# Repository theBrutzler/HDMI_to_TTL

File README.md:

# HDMI_to_TTL

HDMI-Ausgang für das R1gol DS1054Z: Das parallele 24-Bit-RGB-Signal (800 × 480), das vom Mainboard zum internen Display geht, wird abgegriffen und von einem **Tang Nano 9K** (Gowin GW1NR-9C) in ein HDMI-Signal umgewandelt.

*HDMI output for the R1gol DS1054Z: the parallel 24-bit RGB signal (800 × 480) running from the mainboard to the internal display is tapped and converted into an HDMI signal by a **Tang Nano 9K** (Gowin GW1NR-9C).*

Diese Anleitung beschreibt, wie die Platine bestückt und der FPGA programmiert wird.

*This guide describes how to assemble the board and program the FPGA.*

> ⚠️ **Haftungsausschluss:** Nachbau, Programmierung und Einbau erfolgen **auf eigene Gefahr**. Für das Öffnen des Oszilloskops wird ein Eingriff in das Gerät nötig, der zum Verlust der Garantie führen kann. Für Schäden am Oszilloskop, am Tang Nano 9K, an angeschlossenen Geräten oder sonstige Folgeschäden wird **keine Haftung übernommen**.
>
> *⚠️ **Disclaimer:** Building, programming and installing this modification is done **at your own risk**. Opening the oscilloscope requires modifying the device, which may void its warranty. **No liability is accepted** for damage to the oscilloscope, the Tang Nano 9K, connected devices or any other consequential damage.*

---

## Inhalt / *Contents*

1. [Benötigte Teile / *Required parts*](#1-benötigte-teile--required-parts)
2. [Die Platine / *The PCB*](#2-die-platine--the-pcb)
3. [Platine trennen / *Breaking the PCB apart*](#3-platine-trennen--breaking-the-pcb-apart)
4. [Tang Nano 9K bestücken / *Mounting the Tang Nano 9K*](#4-tang-nano-9k-bestücken--mounting-the-tang-nano-9k)
5. [FPGA programmieren / *Programming the FPGA*](#5-fpga-programmieren--programming-the-fpga)
6. [Einbau ins Oszilloskop / *Installation in the oscilloscope*](#6-einbau-ins-oszilloskop--installation-in-the-oscilloscope)
7. [Fehlersuche (LEDs und UART) / *Troubleshooting (LEDs and UART)*](#7-fehlersuche-leds-und-uart--troubleshooting-leds-and-uart)

---

## 1. Benötigte Teile / *Required parts*

| Teil / *Part* | Bemerkung / *Notes* |
|---|---|
| Platine `TTL_to_HDMI`<br>*PCB `TTL_to_HDMI`* | Display-Teil und FPGA-Teil hängen als ein Nutzen zusammen<br>*Display part and FPGA part come as one panel* |
| Tang Nano 9K | Sipeed, FPGA GW1NR-LV9QN88PC6/I5 |
| 2 × Stiftleiste 1 × 24, Raster 2,54 mm<br>*2 × pin header 1 × 24, 2.54 mm pitch* | für den Tang Nano 9K (liegen dem Board meist bei)<br>*for the Tang Nano 9K (usually included with the board)* |
| Buchsenleiste 1 × 2, Raster 2,54 mm<br>*Female header 1 × 2, 2.54 mm pitch* | J1, holt die 5 V von der Stiftleiste des Mainboards<br>*J1, picks up 5 V from the mainboard pin header* |
| FFC-Kabel 50-polig, Raster 0,5 mm<br>*FFC cable 50-pin, 0.5 mm pitch* | verbindet Mainboard und Display-Teil („To Mainboard“)<br>*connects mainboard and display part ("To Mainboard")* |
| FFC-Kabel 35-polig, Raster 0,5 mm<br>*FFC cable 35-pin, 0.5 mm pitch* | verbindet Display-Teil (J5) und FPGA-Teil (J3)<br>*connects display part (J5) and FPGA part (J3)* |
| HDMI-Einbau-Verlängerung mit 90°-Winkelstecker<br>*Panel-mount HDMI extension with 90° angled plug* | Buchse zum Festschrauben im Gehäuse, Stecker in den Tang Nano 9K (siehe [Abschnitt 6.3](#63-hdmi-buchse-im-gehäuse--hdmi-socket-in-the-housing))<br>*socket is screwed into the housing, plug goes into the Tang Nano 9K (see [section 6.3](#63-hdmi-buchse-im-gehäuse--hdmi-socket-in-the-housing))* |
| Isolierband und/oder Kapton-Band<br>*Insulating tape and/or Kapton tape* | zum Fixieren des FPGA-Teils auf dem Mainboard und zum Isolieren des Display-Teils gegen das Metallgehäuse<br>*to fix the FPGA part on the mainboard and to insulate the display part from the metal housing* |
| USB-C-Kabel<br>*USB-C cable* | **nur** zum Programmieren, solange das Board noch nicht eingebaut ist<br>***only** for programming, while the board is not yet installed* |
| PC mit **Gowin EDA / Gowin Programmer**<br>*PC with **Gowin EDA / Gowin Programmer*** | getestet mit Version V1.9.11.03 Education<br>*tested with version V1.9.11.03 Education* |

Die Display-Platine ist bereits mit SMD-Bauteilen bestückt (74HC245-Puffer U4, U6, U7, U8, Widerstände, Kondensatoren, FFC-Stecker).

*The display PCB comes pre-assembled with SMD parts (74HC245 buffers U4, U6, U7, U8, resistors, capacitors, FFC connectors).*

---

## 2. Die Platine / *The PCB*

Die Platine wird als ein Stück geliefert. Links sitzt der FPGA-Teil, rechts der Display-Teil, dazwischen eine Sollbruchstelle.

*The PCB is delivered as one piece. The FPGA part is on the left, the display part on the right, with a break-off line in between.*

**Oberseite** – mit QR-Code, FFC-Steckern und den SMD-Bauteilen:

***Top side** – with QR code, FFC connectors and the SMD parts:*

**Unterseite** – hier ist die Umrisslinie des Tang Nano 9K inklusive Lage der HDMI-Buchse aufgedruckt:

***Bottom side** – the outline of the Tang Nano 9K, including the position of the HDMI socket, is printed here:*

---

## 3. Platine trennen / *Breaking the PCB apart*

Die beiden Teile an der Sollbruchstelle vorsichtig auseinanderbrechen und die Bruchkante bei Bedarf leicht entgraten.

*Carefully break the two parts apart along the break-off line and deburr the edge slightly if necessary.*

**Display-Teil** – kommt ins Oszilloskop zwischen Mainboard und Display. U1/U2 sind die 50-poligen Display-Stecker, J5 ist der 35-polige Anschluss zum FPGA-Teil:

***Display part** – goes into the oscilloscope between mainboard and display. U1/U2 are the 50-pin display connectors, J5 is the 35-pin connection to the FPGA part:*

**FPGA-Teil** – Oberseite mit J3 (35-polig, zum Display-Teil) und J1 (+5 V / GND):

***FPGA part** – top side with J3 (35-pin, to the display part) and J1 (+5 V / GND):*

---

## 4. Tang Nano 9K bestücken / *Mounting the Tang Nano 9K*

Der Tang Nano 9K wird auf der **Unterseite** des FPGA-Teils montiert, also auf der Seite mit der aufgedruckten Umrisslinie (nicht auf der QR-Code-Seite).

*The Tang Nano 9K is mounted on the **bottom side** of the FPGA part, i.e. the side with the printed outline (not the QR code side).*

1. Die beiden Stiftleisten (1 × 24) in den Tang Nano 9K stecken.<br>
   *Insert the two pin headers (1 × 24) into the Tang Nano 9K.*
2. Den Tang Nano 9K so auf die Unterseite der Platine setzen, dass er **in der Umrisslinie** liegt:<br>
   *Place the Tang Nano 9K on the bottom side of the PCB so that it sits **inside the outline**:*
   - die **HDMI-Buchse** zeigt zur Bruchkante (Aufdruck „HDMI“),<br>
     *the **HDMI socket** faces the break-off edge (marking "HDMI"),*
   - die **USB-C-Buchse** zeigt zur Seite mit J1 / J2.<br>
     *the **USB-C socket** faces the side with J1 / J2.*
3. Die Stifte stehen dann auf der Oberseite (QR-Code-Seite) durch und werden dort verlötet.<br>
   *The pins then stick out on the top side (QR code side) and are soldered there.*
4. Zuerst nur je einen Pin an beiden Enden löten, Lage prüfen (Board liegt plan und gerade in der Umrisslinie), dann die restlichen Pins löten.<br>
   *First solder only one pin at each end, check the position (board lies flat and straight inside the outline), then solder the remaining pins.*
5. Überstehende Stifte auf der Oberseite kürzen, damit sie später nichts berühren.<br>
   *Trim the protruding pins on the top side so they don't touch anything later.*

So sieht das bestückte FPGA-Teil aus (Unterseite, noch vor dem Trennen):

*This is what the assembled FPGA part looks like (bottom side, before breaking apart):*

Und nach dem Trennen:

*And after breaking apart:*

6. Die Buchsenleiste **J1** (1 × 2, +5 V / GND) auf derselben Seite wie den Tang Nano 9K einlöten, also auf der Unterseite. Sie wird beim Einbau auf die Stiftleiste des Mainboards gesteckt (siehe [Abschnitt 6.2](#62-fpga-teil-auf-dem-mainboard-befestigen--mounting-the-fpga-part-on-the-mainboard)).<br>
   *Solder the female header **J1** (1 × 2, +5 V / GND) on the same side as the Tang Nano 9K, i.e. the bottom side. During installation it is plugged onto the mainboard pin header (see [section 6.2](#62-fpga-teil-auf-dem-mainboard-befestigen--mounting-the-fpga-part-on-the-mainboard)).*

> **Hinweis:** J2 („ONLY DUMMY“, 2 × 9) wird **nicht** bestückt. Die Löcher dienen nur als Freiraum für die übrigen Pins der Mainboard-Stiftleiste.
>
> ***Note:** J2 ("ONLY DUMMY", 2 × 9) is **not** populated. Its holes only provide clearance for the remaining pins of the mainboard pin header.*

Belegung von J1 (auch auf dem Bestückungsdruck markiert):

*Pinout of J1 (also marked on the silkscreen):*

| J1 Pin | Signal |
|---|---|
| 1 (eckiges Pad / *square pad*) | GND |
| 2 | +5 V |

---

## 5. FPGA programmieren / *Programming the FPGA*

> ⚠️ **Wichtig:** Der Tang Nano 9K muss **vor dem Einbau** ins Oszilloskop fertig programmiert werden. Programmiert wird ausschließlich außerhalb des Geräts – das FPGA-Teil darf dabei **nicht** mit dem Oszilloskop verbunden sein.
>
> *⚠️ **Important:** The Tang Nano 9K must be fully programmed **before installation** in the oscilloscope. Programming is done exclusively outside the device – the FPGA part must **not** be connected to the oscilloscope while doing so.*

Die fertige Konfigurationsdatei liegt im Repository unter:

*The ready-to-use configuration file is located in the repository at:*

```
Software/hdmi_letzter_Ki_Stand/impl/pnr/hdmi.fs
```

Wer das Projekt selbst neu bauen will, öffnet `Software/hdmi_letzter_Ki_Stand/hdmi.gprj` in der Gowin EDA und führt *Synthesize* und *Place & Route* aus – danach liegt die `hdmi.fs` an derselben Stelle.

*If you want to rebuild the project yourself, open `Software/hdmi_letzter_Ki_Stand/hdmi.gprj` in Gowin EDA and run **Synthesize** and **Place & Route** – the `hdmi.fs` will then be created at the same location.*

### 5.1 Programmer starten und Board erkennen / *Start the programmer and detect the board*

1. Tang Nano 9K per USB-C mit dem PC verbinden.<br>
   *Connect the Tang Nano 9K to the PC via USB-C.*
2. **Gowin Programmer** starten (entweder einzeln oder in der Gowin EDA über *Tools → Programmer*).<br>
   *Start the **Gowin Programmer** (either standalone or in Gowin EDA via **Tools → Programmer**).*
3. Mit dem Lupen-Symbol (**Scan Device**) nach dem Board suchen. Es sollte ein Eintrag mit<br>
   *Search for the board using the magnifying glass icon (**Scan Device**). An entry with*
   - Series: `GW1NR`
   - Device: `GW1NR-9C`

   erscheinen. Standardmäßig steht als Operation `SRAM Program` drin.<br>
   *should appear. By default the operation is set to `SRAM Program`.*

> `SRAM Program` lädt die Konfiguration nur in den flüchtigen Speicher – nach dem Ausschalten ist sie wieder weg. Damit der FPGA die Konfiguration dauerhaft behält, muss in den internen Flash geschrieben werden (nächster Schritt).
>
> *`SRAM Program` only loads the configuration into volatile memory – it is lost after power-off. For the FPGA to keep the configuration permanently, it has to be written to the internal flash (next step).*

### 5.2 Flash-Programmierung einstellen / *Set up flash programming*

1. Doppelklick auf die Zeile (Spalte **Operation**) – das Fenster **Device configuration** öffnet sich.<br>
   *Double-click the row (column **Operation**) – the **Device configuration** window opens.*
2. Einstellen:<br>
   *Set:*
   - **Access Mode:** `Embedded Flash Mode`
   - **Operation:** `embFlash Erase,Program`
3. Unter **File name** die Datei `hdmi.fs` auswählen (Pfad siehe oben).<br>
   *Under **File name**, select the file `hdmi.fs` (path see above).*
4. Mit **Save** bestätigen.<br>
   *Confirm with **Save**.*

### 5.3 Programmieren / *Program*

In der Liste steht jetzt als Operation `embFlash Erase,Program` und als FS File der Pfad zur `hdmi.fs`:

*The list now shows `embFlash Erase,Program` as operation and the path to `hdmi.fs` as FS file:*

1. Auf das Symbol mit dem grünen Pfeil (**Program/Configure**) klicken.<br>
   *Click the icon with the green arrow (**Program/Configure**).*
2. Warten, bis im Output-Fenster unten die erfolgreiche Programmierung gemeldet wird.<br>
   *Wait until the output window at the bottom reports successful programming.*
3. Fertig – der FPGA startet ab jetzt bei jedem Einschalten mit der HDMI-Konfiguration.<br>
   *Done – from now on the FPGA starts with the HDMI configuration every time it is powered on.*
4. USB-C-Kabel wieder abziehen. Erst jetzt darf das Board eingebaut werden.<br>
   *Unplug the USB-C cable. Only now may the board be installed.*

> **Board wird nicht gefunden?** Unter **USB Cable Setting** prüfen, ob das Kabel erkannt wird, und ggf. *Query/Detect Cable* ausführen. Unter Windows wird ein passender USB-Treiber benötigt (wird mit der Gowin-Software installiert).
>
> ***Board not found?** Check under **USB Cable Setting** whether the cable is detected and run **Query/Detect Cable** if necessary. On Windows a suitable USB driver is required (installed together with the Gowin software).*

---

## 6. Einbau ins Oszilloskop / *Installation in the oscilloscope*

> ⚠️ Der Einbau erfolgt **auf eigene Gefahr**, es wird **keine Haftung** übernommen. Vor dem Öffnen das Oszilloskop ausschalten und vom Netz trennen.
>
> *⚠️ Installation is done **at your own risk**, **no liability** is accepted. Switch off the oscilloscope and disconnect it from mains before opening it.*

Voraussetzung: Der Tang Nano 9K ist fertig programmiert (siehe [Abschnitt 5](#5-fpga-programmieren--programming-the-fpga)) und das USB-C-Kabel ist abgezogen.

*Prerequisite: the Tang Nano 9K is fully programmed (see [section 5](#5-fpga-programmieren--programming-the-fpga)) and the USB-C cable is unplugged.*

### 6.1 Display-Teil einsetzen / *Installing the display part*

Das Display-Teil wird zwischen Display und **Metallgehäuse** gelegt und in die Verbindung zwischen Mainboard und Display eingeschleift.

*The display part is placed between the display and the **metal housing** and inserted into the connection between mainboard and display.*

> ⚠️ Die Seite des Display-Teils, die zum Metallgehäuse zeigt, mit Isolierband oder Kapton-Band abkleben, damit Lötstellen und Bauteile keinen Kurzschluss zum Gehäuse bekommen.
>
> *⚠️ Cover the side of the display part facing the metal housing with insulating tape or Kapton tape, so that solder joints and components cannot short against the housing.*

1. Das originale Display-Flachbandkabel vom Display abziehen.<br>
   *Unplug the original display ribbon cable from the display.*
2. Das neue **50-polige FFC-Kabel** (Raster 0,5 mm) in den Display-Stecker des **Mainboards** und in den oberen 50-poligen Stecker des Display-Teils („To Mainboard“) stecken.<br>
   *Plug the new **50-pin FFC cable** (0.5 mm pitch) into the display connector of the **mainboard** and into the upper 50-pin connector of the display part ("To Mainboard").*
3. Das Kabel des Displays in den mittleren 50-poligen Stecker („To Display“) stecken.<br>
   *Plug the display cable into the middle 50-pin connector ("To Display").*
4. Das 35-polige FFC-Kabel in den unteren Stecker J5 („To FPGA“) stecken und zum FPGA-Teil führen.<br>
   *Plug the 35-pin FFC cable into the lower connector J5 ("To FPGA") and route it to the FPGA part.*
5. Das Display-Teil (Seite zum Metall isoliert) zwischen Display und Metallgehäuse einlegen.<br>
   *Place the display part (side facing the metal insulated) between display and metal housing.*

### 6.2 FPGA-Teil auf dem Mainboard befestigen / *Mounting the FPGA part on the mainboard*

Das FPGA-Teil liegt auf dem Mainboard, mit der QR-Code-Seite nach oben (der Tang Nano 9K zeigt also zum Mainboard), und wird mit Isolierband fixiert.

*The FPGA part lies on the mainboard with the QR code side facing up (so the Tang Nano 9K faces the mainboard) and is fixed with insulating tape.*

1. Das andere Ende des 35-poligen FFC-Kabels in J3 des FPGA-Teils stecken.<br>
   *Plug the other end of the 35-pin FFC cable into J3 of the FPGA part.*
2. Das FPGA-Teil an der gezeigten Stelle auf das Mainboard legen und dabei auf die Stiftleiste des Mainboards neben dem Summer stecken (roter Kreis im Bild unten). Die Stiftleiste liegt dann unter J2 und J1 zusammen: Die Löcher von J2 nehmen die übrigen Pins auf, die Buchsenleiste **J1** greift die beiden Pins für **GND** (J1 Pin 1) und **+5 V** (J1 Pin 2) ab. Darüber wird das FPGA-Teil mit 5 V aus dem Oszilloskop versorgt.<br>
   *Place the FPGA part on the mainboard at the position shown, plugging it onto the mainboard pin header next to the buzzer (red circle in the picture below). The pin header then sits under J2 and J1 together: the holes of J2 take the remaining pins, the female header **J1** picks up the two pins for **GND** (J1 pin 1) and **+5 V** (J1 pin 2). This supplies the FPGA part with 5 V from the oscilloscope.*

   > Vor dem ersten Einschalten mit einem Multimeter prüfen, ob die Platine richtig und nicht versetzt aufgesteckt ist und an J1 tatsächlich +5 V gegen GND anliegen.
   >
   > *Before powering on for the first time, use a multimeter to check that the board is plugged on correctly and not offset, and that +5 V against GND is actually present at J1.*
3. Darauf achten, dass die gekürzten Pins und die Bauteile des Tang Nano 9K keinen Kontakt zu Bauteilen oder Leiterbahnen des Mainboards haben.<br>
   *Make sure that the trimmed pins and the components of the Tang Nano 9K do not touch any components or traces of the mainboard.*
4. Das FPGA-Teil mit Isolierband auf dem Mainboard fixieren.<br>
   *Fix the FPGA part on the mainboard with insulating tape.*

So sieht es eingebaut aus. Links und rechts hält Isolierband die Platine, unten kommt das FFC-Kabel vom Display-Teil, rechts geht das HDMI-Kabel ab:

*This is what it looks like installed. Insulating tape holds the board on the left and right, the FFC cable from the display part comes in at the bottom, the HDMI cable leaves to the right:*

### 6.3 HDMI-Buchse im Gehäuse / *HDMI socket in the housing*

Damit das HDMI-Signal nach außen kommt, wird eine kurze HDMI-Einbau-Verlängerung verwendet: Auf der einen Seite ist ein 90°-Winkelstecker, auf der anderen eine Buchse mit zwei Schraublaschen.

*To bring the HDMI signal outside, a short panel-mount HDMI extension is used: one end has a 90° angled plug, the other a socket with two screw tabs.*

1. Den Winkelstecker in die HDMI-Buchse des Tang Nano 9K stecken.<br>
   *Plug the angled plug into the HDMI socket of the Tang Nano 9K.*
2. Die Position der Buchse in der Gehäuserückwand anzeichnen (oberhalb von USB-B und LAN), Ausschnitt und zwei Bohrungen für die Schrauben anfertigen.<br>
   *Mark the position of the socket on the rear housing (above USB-B and LAN), then make the cut-out and two holes for the screws.*
3. Die Buchse von innen einsetzen und festschrauben.<br>
   *Insert the socket from the inside and screw it in place.*
4. Gehäuse wieder schließen.<br>
   *Close the housing again.*

### 6.4 Inbetriebnahme / *Commissioning*

1. Monitor an die neue HDMI-Buchse anschließen.<br>
   *Connect a monitor to the new HDMI socket.*
2. Oszilloskop einschalten – das Bild erscheint parallel auf dem internen Display und auf dem Monitor.<br>
   *Switch on the oscilloscope – the image appears on the internal display and on the monitor at the same time.*

> ⚠️ **Keine Versorgung über USB-C!** Im eingebauten Zustand darf am Tang Nano 9K **kein USB-C-Kabel** angeschlossen werden. Die 5 V kommen ausschließlich aus dem Oszilloskop über J1. Ein zusätzlich angeschlossenes USB-Kabel würde zwei 5-V-Quellen gegeneinander schalten und kann Oszilloskop, Tang Nano 9K oder den PC beschädigen.
>
> *⚠️ **No power via USB-C!** When installed, **no USB-C cable** may be connected to the Tang Nano 9K. The 5 V come exclusively from the oscilloscope via J1. An additionally connected USB cable would connect two 5 V sources against each other and can damage the oscilloscope, the Tang Nano 9K or the PC.*

Der FPGA erzeugt den HDMI-Takt selbst aus dem 27-MHz-Oszillator des Tang Nano 9K (Ausgabe 1579 × 525 bei 36 MHz Pixeltakt). Das Eingangsbild wird zwischengepuffert, die Bildrate des Oszilloskops bleibt erhalten.

*The FPGA generates the HDMI clock itself from the 27 MHz oscillator of the Tang Nano 9K (output 1579 × 525 at 36 MHz pixel clock). The input image is buffered and the oscilloscope's frame rate is preserved.*

---

## 7. Fehlersuche (LEDs und UART) / *Troubleshooting (LEDs and UART)*

### LEDs auf dem Tang Nano 9K / *LEDs on the Tang Nano 9K*

| LED | leuchtet, wenn … / *lit when …* |
|---|---|
| 0 | Eingangspuffer (74HC245) freigegeben<br>*input buffer (74HC245) enabled* |
| 1 | Pixeltakt (PCLK) vom Oszilloskop vorhanden<br>*pixel clock (PCLK) from the oscilloscope present* |
| 2 | PLL eingerastet<br>*PLL locked* |
| 3 | HSYNC vorhanden<br>*HSYNC present* |
| 4 | Bilder (DE) werden empfangen<br>*frames (DE) are being received* |
| 5 | Testbild-Modus aktiv<br>*test pattern mode active* |

### UART-Konsole / *UART console*

Über den USB-Anschluss des Tang Nano 9K steht eine serielle Konsole zur Verfügung (**115200 Baud, 8N1**). Sie gibt jede Sekunde eine Statuszeile mit den gemessenen Eingangssignalen aus.

*A serial console is available via the USB port of the Tang Nano 9K (**115200 baud, 8N1**). It prints a status line with the measured input signals every second.*

> ⚠️ Die Konsole nur **außerhalb des Oszilloskops** nutzen (Board nur über USB versorgt, nicht mit dem Oszilloskop verbunden) – siehe Warnung in [Abschnitt 6](#6-einbau-ins-oszilloskop--installation-in-the-oscilloscope).
>
> *⚠️ Only use the console **outside the oscilloscope** (board powered via USB only, not connected to the oscilloscope) – see the warning in [section 6](#6-einbau-ins-oszilloskop--installation-in-the-oscilloscope).*

| Befehl / *Command* | Funktion / *Function* |
|---|---|
| `t` | Testbild ein/aus (gleiches HDMI-Timing wie im Normalbetrieb)<br>*test pattern on/off (same HDMI timing as in normal operation)* |
| `?` | Hilfe<br>*help* |

Mit dem Testbild lässt sich vor dem Einbau prüfen, ob die HDMI-Ausgabe funktioniert: Board per USB anschließen, Monitor an HDMI, in der Konsole `t` senden.

*The test pattern lets you check before installation whether the HDMI output works: connect the board via USB, connect a monitor to HDMI, send `t` in the console.*

---

## Links

- GitHub: https://github.com/theBrutzler/HDMI_to_TTL
- Twitch: https://www.twitch.tv/thebrutzler
- Ko-fi: https://ko-fi.com/thebrutzler

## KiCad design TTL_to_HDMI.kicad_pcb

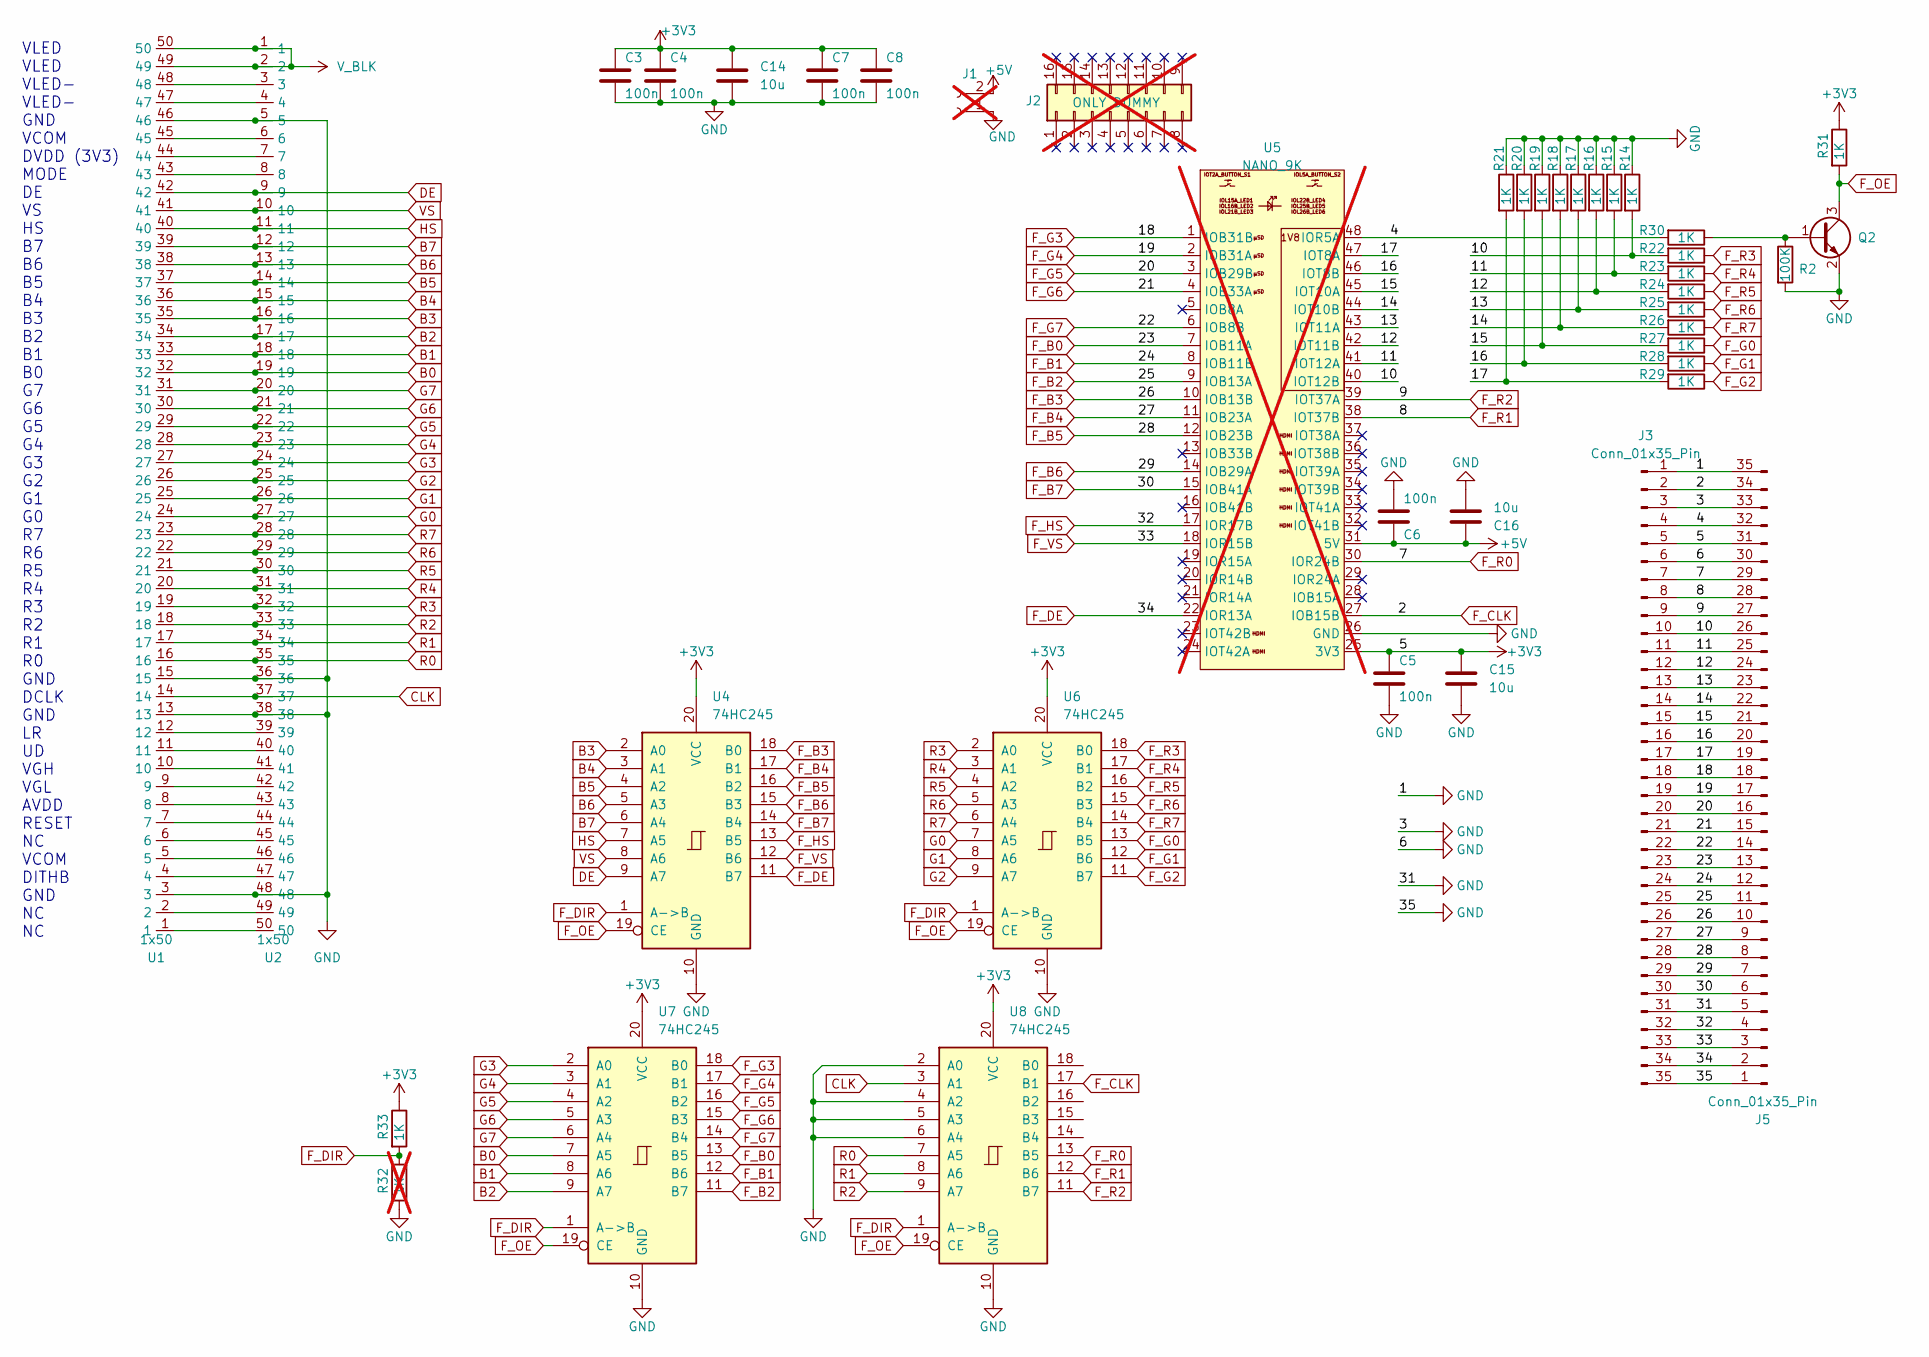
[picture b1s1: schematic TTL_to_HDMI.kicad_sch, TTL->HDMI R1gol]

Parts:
C3, C4, C5, C6, C7, C8: 100n; C_0603_1608Metric; LCSC C6119883
C14, C15, C16: 10u; C_0603_1608Metric; LCSC Part C6119842
J1: Conn_01x02_Socket; PinHeader_1x02_P2.54mm_Vertical; LCSC DNP; not fitted
J2: ONLY DUMMY; PinHeader_2x09_P2.54mm_Vertical; LCSC DNP; not fitted
J3, J5: Conn_01x35_Pin; Amphenol_F32Q-1A7x1-11035_1x35-1MP_P0.5mm_Horizontal; LCSC C2932729
Q2: Q_NPN_BEC; SOT-23; LCSC C181167
R2: 100K; R_0603_1608Metric; LCSC C54920958
R14, R15, R16, R17, R18, R19, R20, R21, R22, R23, R24, R25, R26, R27, R28, R29, R30, R31, R33: 1K; R_0603_1608Metric; LCSC C54920984
R32: 1K; R_0603_1608Metric; LCSC C54920984; not fitted
U1, U2: 1x50; Hirose_FH12-50S-0.5SH_1x50-1MP_P0.50mm_Horizontal; LCSC C22459571
U4, U6, U7, U8: 74HC245; TSSOP-20_4.4x6.5mm_P0.65mm; LCSC C53436307
U5: NANO_9K; Nano 9K; LCSC DNP; not fitted

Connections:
+3V3: C3.2, C4.2, C5.2, C7.2, C8.2, C14.1, C15.1, J3.5, J5.31, R31.1, R33.1, U4.20 (VCC), U5.25 (3V3), U6.20 (VCC), U7.20 (VCC), U8.20 (VCC)
+5V: C6.2, C16.1, J1.2, U5.31 (5V)
/4: J3.4, J5.32, R30.2, U5.48 (IOR5A)
/10: J3.10, J5.26, R14.2, R22.2, U5.40 (IOT12B)
/11: J3.11, J5.25, R15.2, R23.2, U5.41 (IOT12A)
/12: J3.12, J5.24, R16.2, R24.2, U5.42 (IOT11B)
/13: J3.13, J5.23, R17.2, R25.2, U5.43 (IOT11A)
/14: J3.14, J5.22, R18.2, R26.2, U5.44 (IOT10B)
/15: J3.15, J5.21, R19.2, R27.2, U5.45 (IOT10A)
/16: J3.16, J5.20, R20.2, R28.2, U5.46 (IOT8B)
/17: J3.17, J5.19, R21.2, R29.2, U5.47 (IOT8A)
B0: U1.32, U2.19, U7.7 (A5)
B1: U1.33, U2.18, U7.8 (A6)
B2: U1.34, U2.17, U7.9 (A7)
B3: U1.35, U2.16, U4.2 (A0)
B4: U1.36, U2.15, U4.3 (A1)
B5: U1.37, U2.14, U4.4 (A2)
B6: U1.38, U2.13, U4.5 (A3)
B7: U1.39, U2.12, U4.6 (A4)
CLK: U1.14, U2.37, U8.3 (A1)
DE: U1.42, U2.9, U4.9 (A7)
F_B0: J3.23, J5.13, U5.7 (IOB11A), U7.13 (B5)
F_B1: J3.24, J5.12, U5.8 (IOB11B), U7.12 (B6)
F_B2: J3.25, J5.11, U5.9 (IOB13A), U7.11 (B7)
F_B3: J3.26, J5.10, U4.18 (B0), U5.10 (IOB13B)
F_B4: J3.27, J5.9, U4.17 (B1), U5.11 (IOB23A)
F_B5: J3.28, J5.8, U4.16 (B2), U5.12 (IOB23B)
F_B6: J3.29, J5.7, U4.15 (B3), U5.14 (IOB29A)
F_B7: J3.30, J5.6, U4.14 (B4), U5.15 (IOB41A)
F_CLK: J3.2, J5.34, U5.27 (IOB15B), U8.17 (B1)
F_DE: J3.34, J5.2, U4.11 (B7), U5.22 (IOR13A)
F_DIR: R32.1, R33.2, U4.1 (A->B), U6.1 (A->B), U7.1 (A->B), U8.1 (A->B)
F_G0: R27.1, U6.13 (B5)
F_G1: R28.1, U6.12 (B6)
F_G2: R29.1, U6.11 (B7)
F_G3: J3.18, J5.18, U5.1 (IOB31B), U7.18 (B0)
F_G4: J3.19, J5.17, U5.2 (IOB31A), U7.17 (B1)
F_G5: J3.20, J5.16, U5.3 (IOB29B), U7.16 (B2)
F_G6: J3.21, J5.15, U5.4 (IOB33A), U7.15 (B3)
F_G7: J3.22, J5.14, U5.6 (IOB8B), U7.14 (B4)
F_HS: J3.32, J5.4, U4.13 (B5), U5.17 (IOR17B)
F_OE: Q2.3 (C), R31.2, U4.19 (CE), U6.19 (CE), U7.19 (CE), U8.19 (CE)
F_R0: J3.7, J5.29, U5.30 (IOR24B), U8.13 (B5)
F_R1: J3.8, J5.28, U5.38 (IOT37B), U8.12 (B6)
F_R2: J3.9, J5.27, U5.39 (IOT37A), U8.11 (B7)
F_R3: R22.1, U6.18 (B0)
F_R4: R23.1, U6.17 (B1)
F_R5: R24.1, U6.16 (B2)
F_R6: R25.1, U6.15 (B3)
F_R7: R26.1, U6.14 (B4)
F_VS: J3.33, J5.3, U4.12 (B6), U5.18 (IOR15B)
G0: U1.24, U2.27, U6.7 (A5)
G1: U1.25, U2.26, U6.8 (A6)
G2: U1.26, U2.25, U6.9 (A7)
G3: U1.27, U2.24, U7.2 (A0)
G4: U1.28, U2.23, U7.3 (A1)
G5: U1.29, U2.22, U7.4 (A2)
G6: U1.30, U2.21, U7.5 (A3)
G7: U1.31, U2.20, U7.6 (A4)
GND: C3.1, C4.1, C5.1, C6.1, C7.1, C8.1, C14.2, C15.2, C16.2, J1.1, J3.1, J3.3, J3.6, J3.31, J3.35, J5.1, J5.5, J5.30, J5.33, J5.35, Q2.2 (E), R2.2, R14.1, R15.1, R16.1, R17.1, R18.1, R19.1, R20.1, R21.1, R32.2, U1.3, U1.13, U1.15, U1.46, U2.5, U2.36, U2.38, U2.48, U4.10 (GND), U5.26 (GND), U6.10 (GND), U7.10 (GND), U8.2 (A0), U8.4 (A2), U8.5 (A3), U8.6 (A4), U8.10 (GND)
HS: U1.40, U2.11, U4.7 (A5)
unnamed: Q2.1 (B), R2.1, R30.1
unnamed: U1.1, U2.50
unnamed: U1.2, U2.49
unnamed: U1.4, U2.47
unnamed: U1.5, U2.46
unnamed: U1.6, U2.45
unnamed: U1.7, U2.44
unnamed: U1.8, U2.43
unnamed: U1.9, U2.42
unnamed: U1.10, U2.41
unnamed: U1.11, U2.40
unnamed: U1.12, U2.39
unnamed: U1.43, U2.8
unnamed: U1.44, U2.7
unnamed: U1.45, U2.6
unnamed: U1.47, U2.4
unnamed: U1.48, U2.3
R0: U1.16, U2.35, U8.7 (A5)
R1: U1.17, U2.34, U8.8 (A6)
R2: U1.18, U2.33, U8.9 (A7)
R3: U1.19, U2.32, U6.2 (A0)
R4: U1.20, U2.31, U6.3 (A1)
R5: U1.21, U2.30, U6.4 (A2)
R6: U1.22, U2.29, U6.5 (A3)
R7: U1.23, U2.28, U6.6 (A4)
VS: U1.41, U2.10, U4.8 (A6)
V_BLK: U1.49, U1.50, U2.1, U2.2

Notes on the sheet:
VLED VLED VLED- VLED- GND VCOM DVDD (3V3) MODE DE VS HS B7 B6 B5 B4 B3 B2 B1 B0 G7 G6 G5 G4 G3 G2 G1 G0 R7 R6 R5 R4 R3 R2 R1 R0 GND DCLK GND LR UD VGH VGL AVDD RESET NC VCOM DITHB GND NC NC

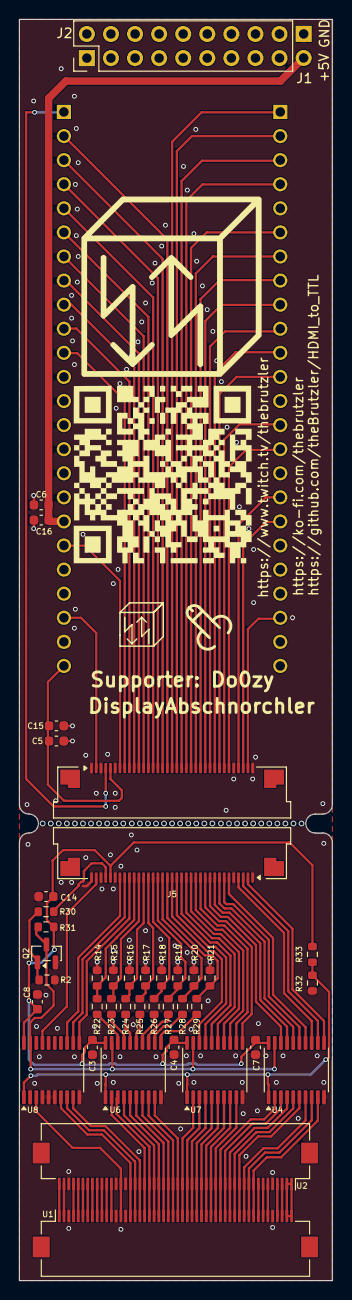
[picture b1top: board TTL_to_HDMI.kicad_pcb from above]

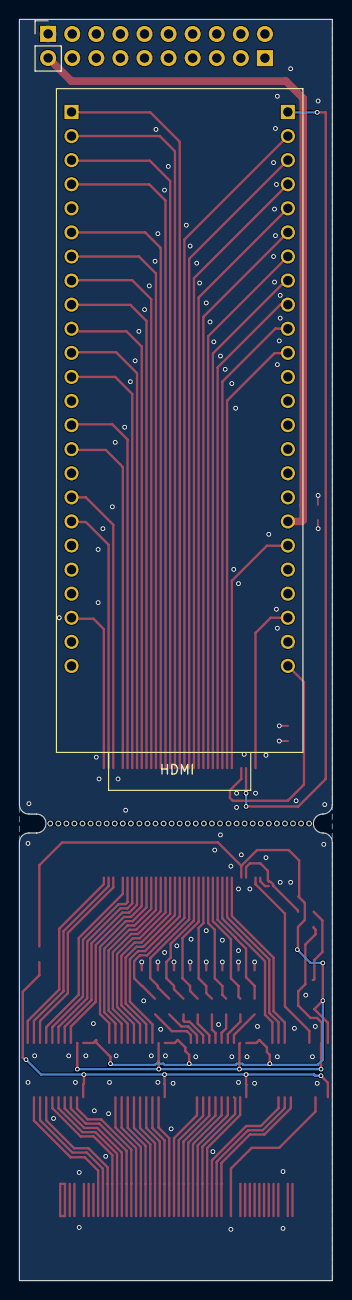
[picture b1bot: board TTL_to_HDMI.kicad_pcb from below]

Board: 2 copper layers, 33.0 x 133.0 mm, 43 parts (2 on the bottom side), 88 nets.

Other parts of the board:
SM3: SYM_Arrow45_Tiny; Symbol_kurzschlussblog

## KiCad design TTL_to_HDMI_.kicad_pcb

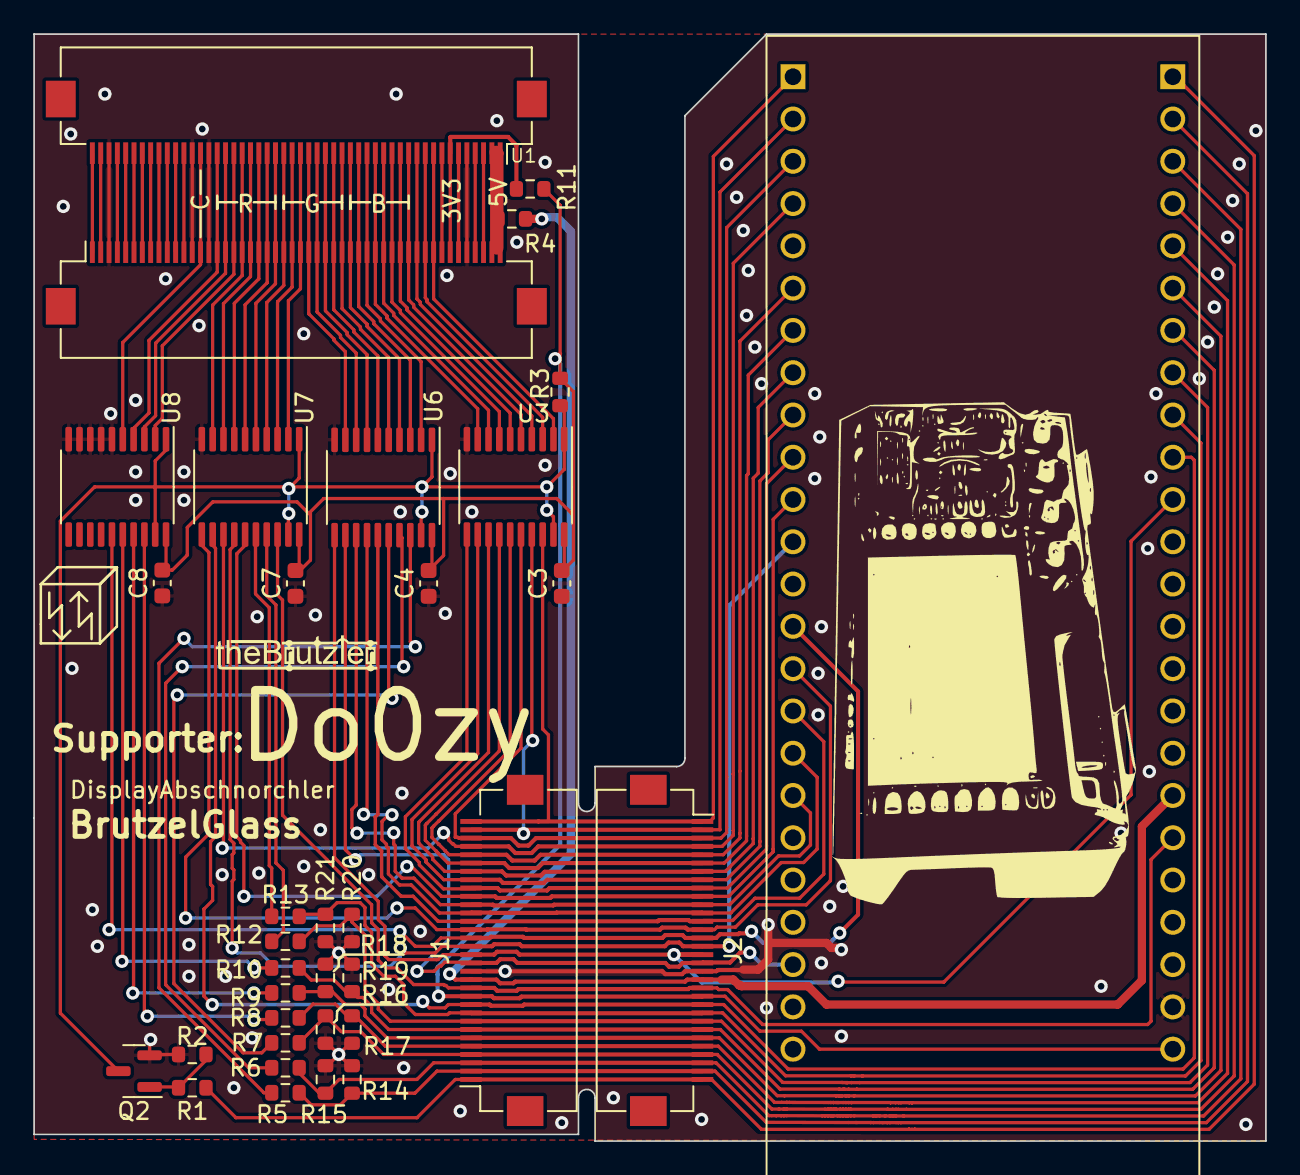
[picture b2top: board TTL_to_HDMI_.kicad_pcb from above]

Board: 2 copper layers, 74.0 x 66.5 mm, 36 parts (0 on the bottom side), 87 nets.

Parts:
C3, C4, C7, C8: 100n; C_0603_1608Metric
J1, J2: Conn_01x32_Pin; Hirose_FH12-32S-0.5SH_1x32-1MP_P0.50mm_Horizontal
Q2: Q_NPN_BEC; SOT-23
R1, R3, R5, R6, R7, R8, R9, R10, R12, R13, R14, R15, R16, R17, R18, R19, R20, R21: 10K; R_0603_1608Metric
R2: 100K; R_0603_1608Metric
R4, R11: 0; R_0603_1608Metric
SM3: SYM_Arrow45_Tiny; Symbol_kurzschlussblog
U1, U2: 1x50; Hirose_FH12-50S-0.5SH_1x50-1MP_P0.50mm_Horizontal
U3, U6, U7, U8: 74LVX541; TSSOP-20_4.4x6.5mm_P0.65mm
U5: NANO_9K; Nano 9K

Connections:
+3V3: C3.2, C4.2, C7.2, C8.2, J1.11, J2.22, R3.1, R11.2, U3.20 (VCC), U5.25 (3V3), U6.20 (VCC), U7.20 (VCC), U8.20 (VCC)
+5V: J1.13, J2.20, R4.2, U5.31 (5V)
/24: J1.9, J2.24, R13.2, R21.2, U5.40 (IOT12B)
/25: J1.8, J2.25, R12.2, R20.2, U5.41 (IOT12A)
/26: J1.7, J2.26, R10.2, R19.2, U5.42 (IOT11B)
/27: J1.6, J2.27, R9.2, R18.2, U5.43 (IOT11A)
/28: J1.5, J2.28, R8.2, R17.2, U5.44 (IOT10B)
/29: J1.4, J2.29, R7.2, R16.2, U5.45 (IOT10A)
/30: J1.3, J2.30, R6.2, R15.2, U5.46 (IOT8B)
/31: J1.2, J2.31, R5.2, R14.2, U5.47 (IOT8A)
/32: J1.1, J2.32, R1.2, U5.48 (IOR5A)
B0: U1.19, U2.32, U6.4 (A2)
B1: U1.18, U2.33, U6.3 (A1)
B2: U1.17, U2.34, U6.2 (A0)
B3: U1.16, U2.35, U3.9 (A7)
B4: U1.15, U2.36, U3.8 (A6)
B5: U1.14, U2.37, U3.7 (A5)
B6: U1.13, U2.38, U3.6 (A4)
B7: U1.12, U2.39, U3.5 (A3)
CLK: U1.37, U2.14, U8.5 (A3)
DE: U1.9, U2.42, U3.2 (A0)
F_B0: R7.1, U6.16 (Y2)
F_B1: R6.1, U6.17 (Y1)
F_B2: R5.1, U6.18 (Y0)
F_B3: J1.24, J2.9, U3.11 (Y7), U5.10 (IOB13B)
F_B4: J1.25, J2.8, U3.12 (Y6), U5.9 (IOB13A)
F_B5: J1.26, J2.7, U3.13 (Y5), U5.8 (IOB11B)
F_B6: J1.27, J2.6, U3.14 (Y4), U5.7 (IOB11A)
F_B7: J1.28, J2.5, U3.15 (Y3), U5.6 (IOB8B)
F_CLK: J1.18, J2.15, U5.14 (IOB29A), U8.15 (Y3)
F_DE: J1.32, J2.1, U3.18 (Y0), U5.1 (IOB31B)
F_G0: R13.1, U7.16 (Y2)
F_G1: R12.1, U7.17 (Y1)
F_G2: J1.12, J2.21, U5.30 (IOR24B), U7.18 (Y0)
F_G3: J1.16, J2.17, U5.38 (IOT37B), U6.11 (Y7)
F_G4: J1.15, J2.18, U5.22 (IOR13A), U6.12 (Y6)
F_G5: J1.22, J2.11, U5.18 (IOR15B), U6.13 (Y5)
F_G6: J1.21, J2.12, U5.17 (IOR17B), U6.14 (Y4)
F_G7: J1.20, J2.13, U5.16 (IOB41B), U6.15 (Y3)
F_HS: J1.30, J2.3, U3.16 (Y2), U5.3 (IOB29B)
F_OE1: Q2.3 (C), R3.2, U3.1 (G1), U3.19 (G2), U6.1 (G1), U6.19 (G2), U7.1 (G1), U7.19 (G2), U8.1 (G1), U8.19 (G2)
F_R0: R10.1, U8.16 (Y2)
F_R1: R9.1, U8.17 (Y1)
F_R2: R8.1, U8.18 (Y0)
F_R3: J1.19, J2.14, U5.15 (IOB41A), U7.11 (Y7)
F_R4: J1.10, J2.23, U5.39 (IOT37A), U7.12 (Y6)
F_R5: J1.29, J2.4, U5.4 (IOB33A), U7.13 (Y5)
F_R6: J1.17, J2.16, U5.12 (IOB23B), U7.14 (Y4)
F_R7: J1.23, J2.10, U5.11 (IOB23A), U7.15 (Y3)
F_VS: J1.31, J2.2, U3.17 (Y1), U5.2 (IOB31A)
G0: U1.27, U2.24, U7.4 (A2)
G1: U1.26, U2.25, U7.3 (A1)
G2: U1.25, U2.26, U7.2 (A0)
G3: U1.24, U2.27, U6.9 (A7)
G4: U1.23, U2.28, U6.8 (A6)
G5: U1.22, U2.29, U6.7 (A5)
G6: U1.21, U2.30, U6.6 (A4)
G7: U1.20, U2.31, U6.5 (A3)
GND: C3.1, C4.1, C7.1, C8.1, J1.14, J2.19, Q2.2 (E), R2.2, R14.1, R15.1, R16.1, R17.1, R18.1, R19.1, R20.1, R21.1, U1.5, U1.36, U1.38, U1.48, U2.3, U2.13, U2.15, U2.46, U3.10 (GND), U5.26 (GND), U6.10 (GND), U7.10 (GND), U8.6 (A4), U8.7 (A5), U8.8 (A6), U8.9 (A7), U8.10 (GND)
HS: U1.11, U2.40, U3.4 (A2)
unnamed: Q2.1 (B), R1.1, R2.1
unnamed: R4.1, U1.1, U1.2, U2.49, U2.50
unnamed: U1.3, U2.48
unnamed: U1.4, U2.47
unnamed: U1.6, U2.45
unnamed: U1.8, U2.43
unnamed: U1.39, U2.12
unnamed: U1.40, U2.11
unnamed: U1.41, U2.10
unnamed: U1.42, U2.9
unnamed: U1.43, U2.8
unnamed: U1.44, U2.7
unnamed: U1.45, U2.6
unnamed: U1.46, U2.5
unnamed: U1.47, U2.4
unnamed: U1.49, U2.2
unnamed: U1.50, U2.1
R0: U1.35, U2.16, U8.4 (A2)
R1: U1.34, U2.17, U8.3 (A1)
R2: U1.33, U2.18, U8.2 (A0)
R3: U1.32, U2.19, U7.9 (A7)
R4: U1.31, U2.20, U7.8 (A6)
R5: U1.30, U2.21, U7.7 (A5)
R6: U1.29, U2.22, U7.6 (A4)
R7: U1.28, U2.23, U7.5 (A3)
VCC: R11.1, U1.7, U2.44
VS: U1.10, U2.41, U3.3 (A1)

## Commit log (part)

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2022-11-29 Initial Upload
    NOT WORKING!
2022-12-04 Add kibot action to generate schematic
2022-12-04 Disable preflight checks because of errors in the design
2022-12-05 Update generate_schematic_pdf.yaml
    only generate if not there
2024-02-11 Upload_V3 V4 and PDF V3
